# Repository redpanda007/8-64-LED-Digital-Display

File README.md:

# 8*64 LED Digital Display

Welcome to the 8*64 LED Digital Display project repository. This project showcases the design of a large-scale LED matrix display, perfect for digital signage, information boards, or creative lighting installations.

## Project Description

This repository contains the design files for an 8*64 LED digital display. The display consists of a matrix of 8 rows and 64 columns of LEDs, providing a versatile canvas for displaying text, graphics, and animations.

## Design Files

### Schematic Diagram
View the electrical schematic for the LED matrix:
[Schematic Diagram](https://a360.co/3yEBdw0)

### PCB Design
Explore the 2D PCB layout:
[2D PCB Design](https://a360.co/3Mn7vhW)

### 3D PCB Model
Visualize the PCB in 3D:
[3D PCB Design](https://a360.co/4cF3tME)

## Features

- 8*64 LED matrix configuration
- Custom PCB design optimized for LED arrangement
- Scalable design for various display sizes

## Applications

- Public information displays
- Advertising billboards
- Event information boards
- Interactive art installations
- Sports scoreboards

## Getting Started

1. Review the schematic diagram to understand the circuit layout.
2. Examine the 2D PCB design for component placement and routing.
3. Use the 3D PCB model to visualize the final product and plan assembly.

## Contributing

We welcome contributions to improve the design or documentation. Please follow these steps:

1. Fork the repository
2. Create a new branch (`git checkout -b feature/AmazingFeature`)
3. Commit your changes (`git commit -m 'Add some AmazingFeature'`)
4. Push to the branch (`git push origin feature/AmazingFeature`)
5. Open a Pull Request

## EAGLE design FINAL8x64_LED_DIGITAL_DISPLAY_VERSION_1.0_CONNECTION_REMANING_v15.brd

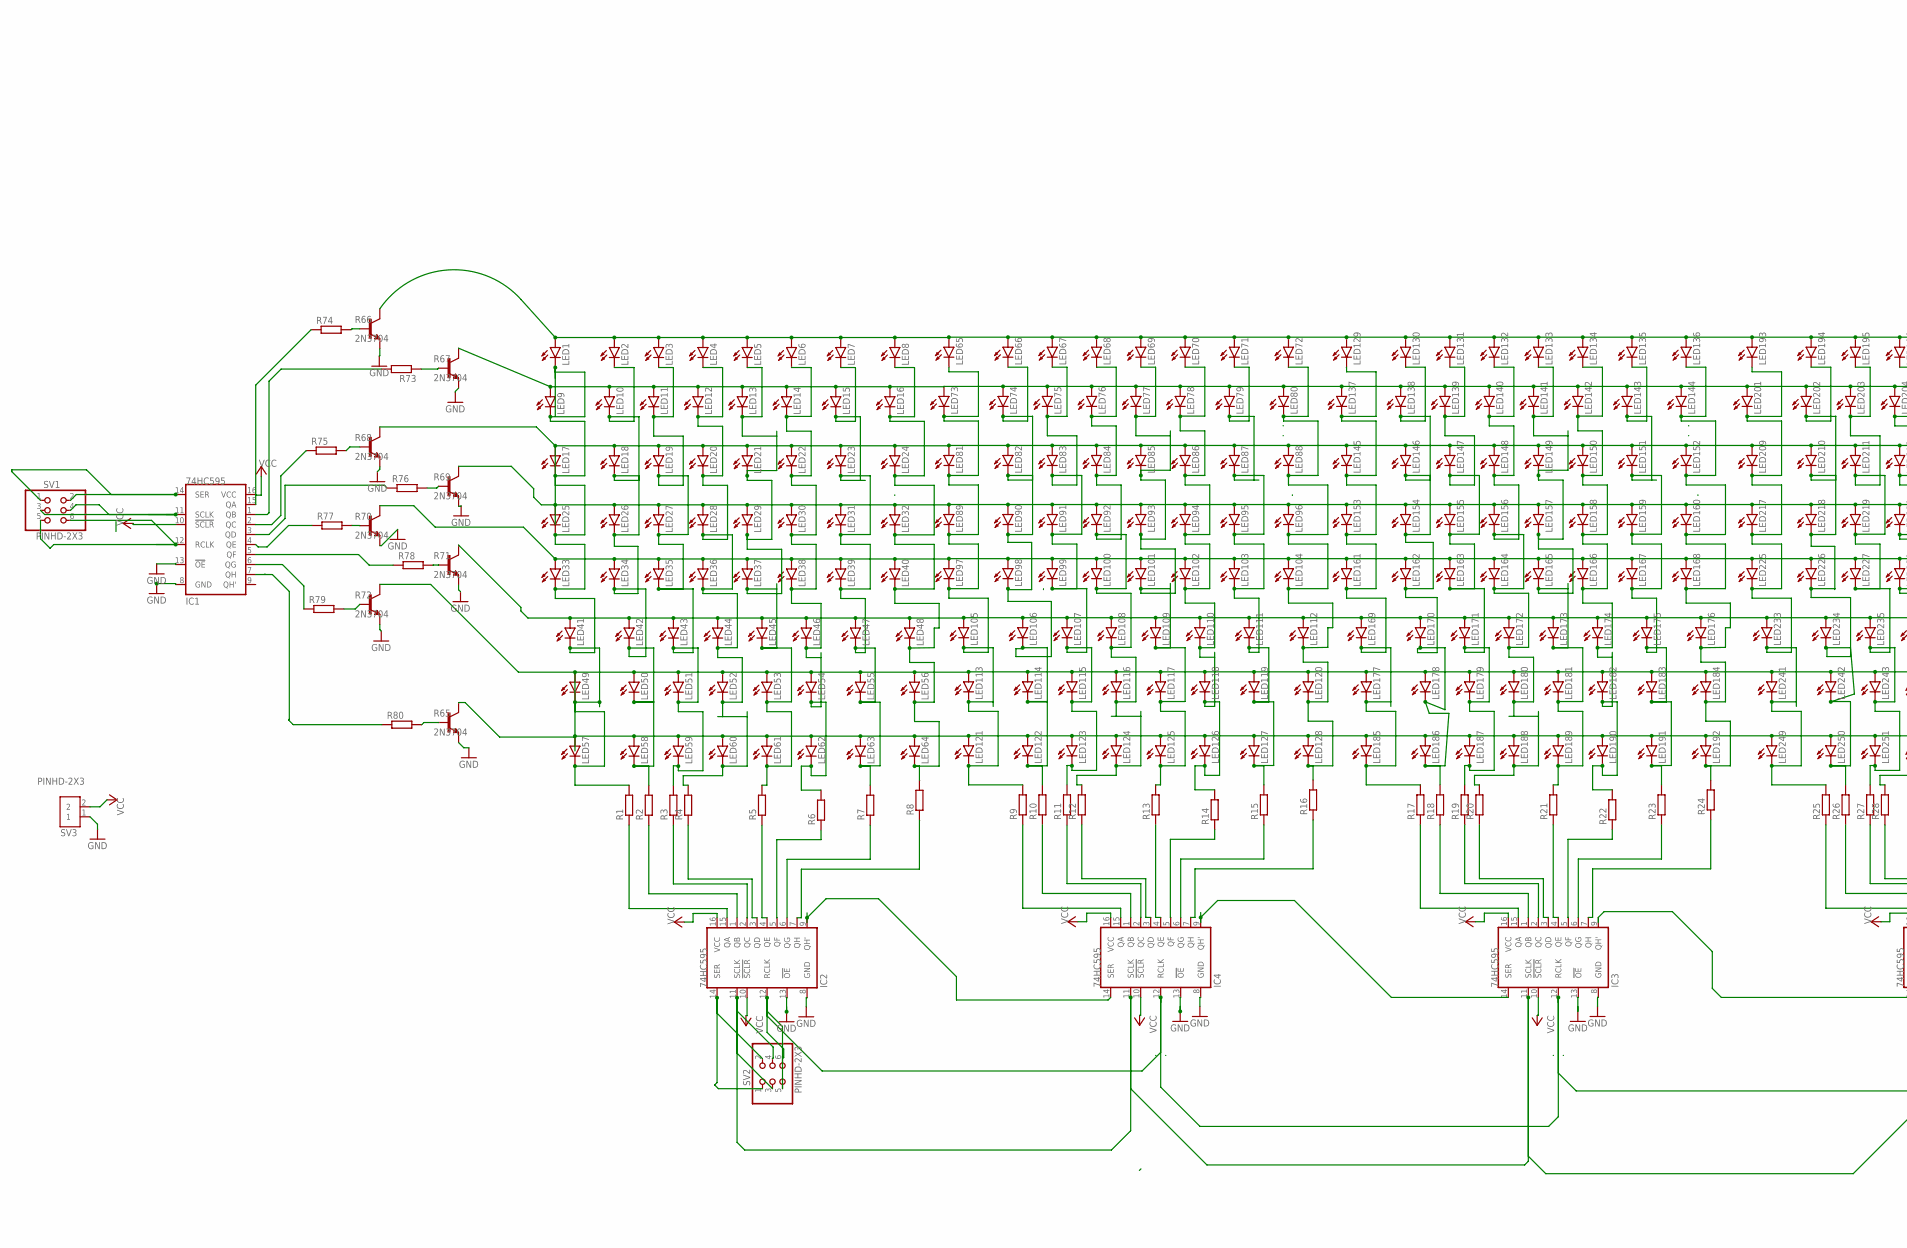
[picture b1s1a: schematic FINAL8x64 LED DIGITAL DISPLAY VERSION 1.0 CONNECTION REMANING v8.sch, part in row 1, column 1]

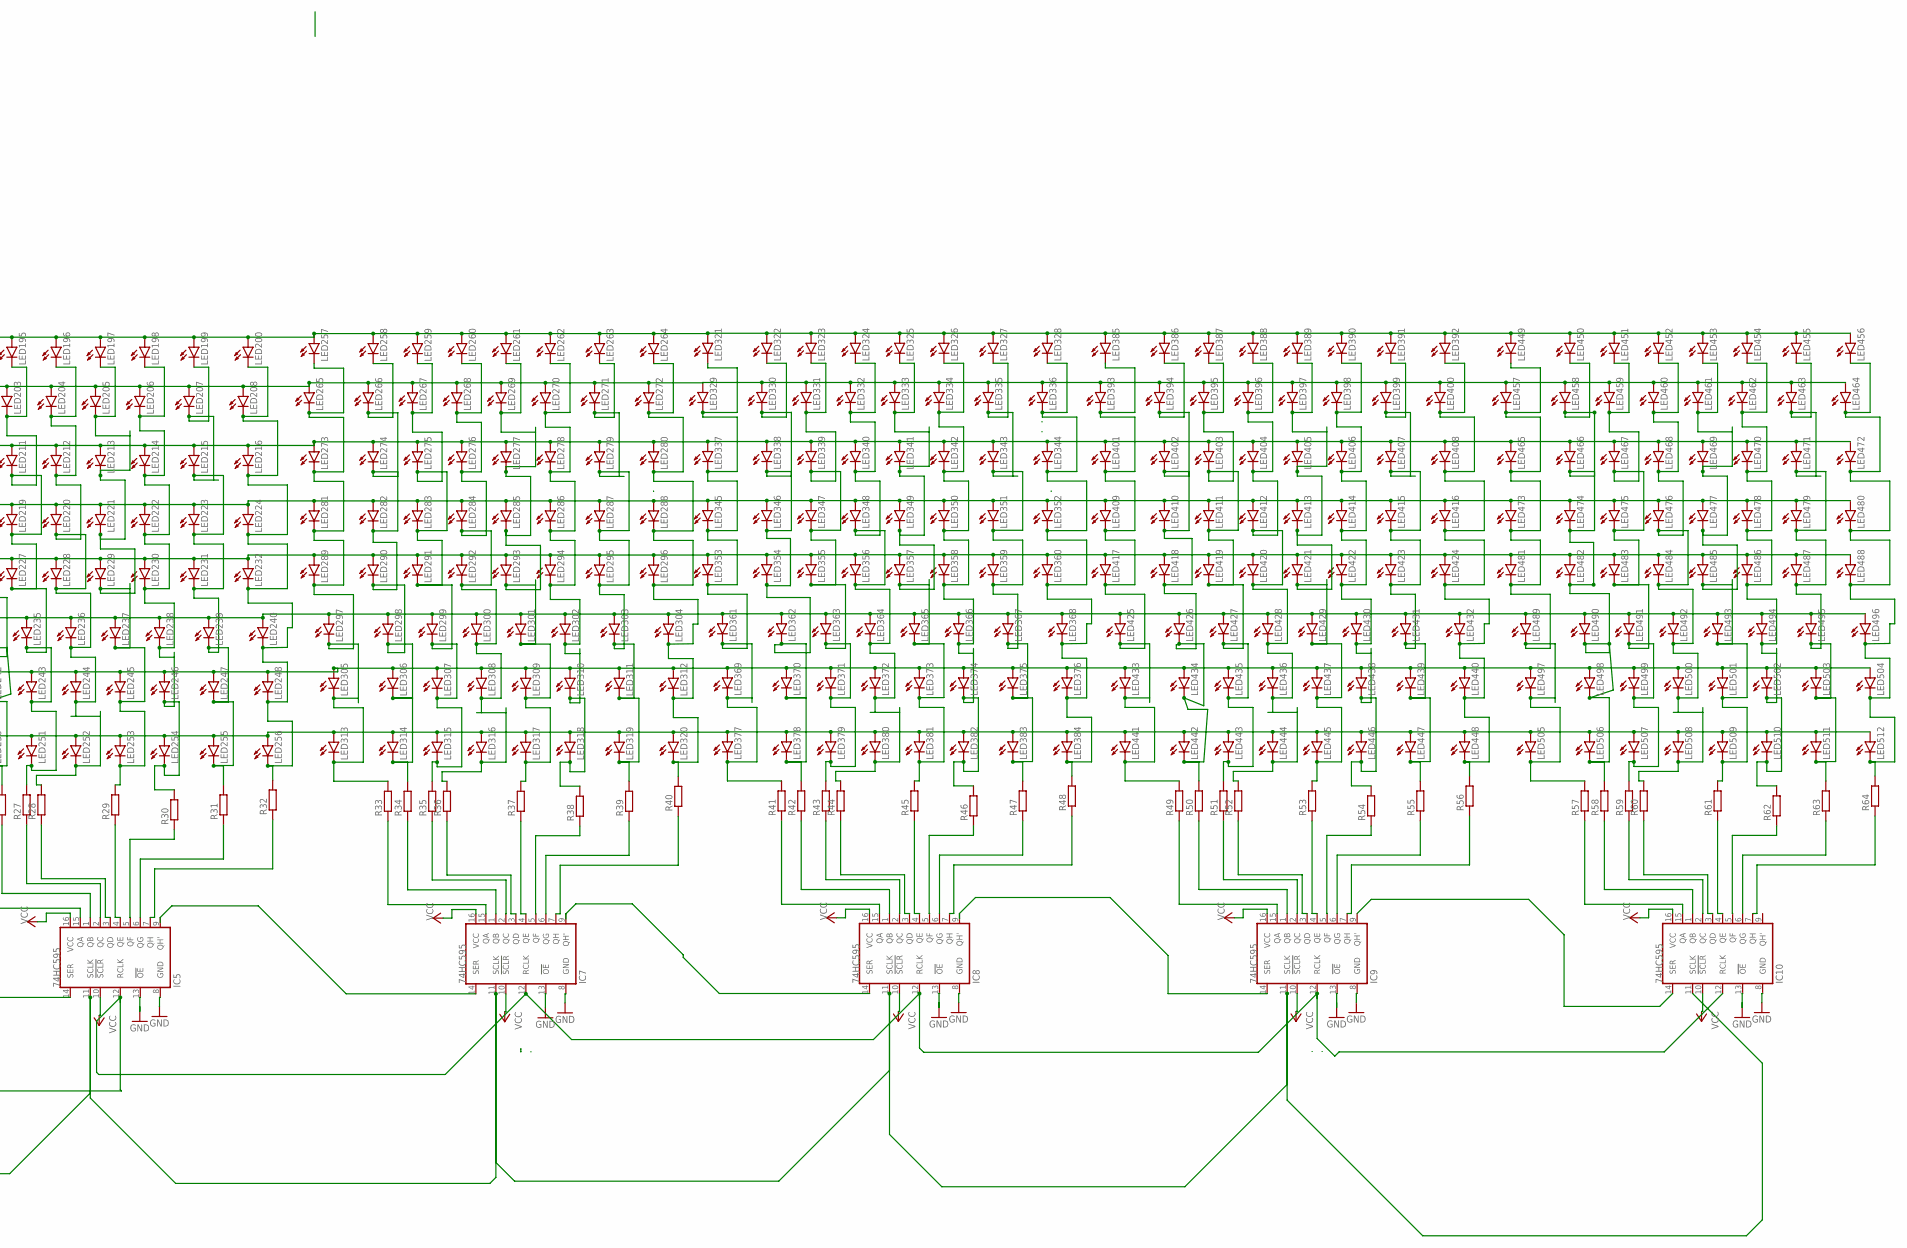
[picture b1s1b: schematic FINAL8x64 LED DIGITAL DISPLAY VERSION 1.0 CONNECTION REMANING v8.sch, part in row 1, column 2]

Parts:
IC1, IC2, IC3, IC4, IC5, IC7, IC8, IC9, IC10: 74HC595; SO16
LED1, LED2, LED3, LED4, LED5, LED6, LED7, LED8, LED9, LED10, LED11, LED12, LED13, LED14, LED15, LED16, LED17, LED18, LED19, LED20, LED21, LED22, LED23, LED24, LED25, LED26, LED27, LED28, LED29, LED30, LED31, LED32, LED33, LED34, LED35, LED36, LED37, LED38, LED39, LED40, LED41, LED42, LED43, LED44, LED45, LED46, LED47, LED48, LED49, LED50, LED51, LED52, LED53, LED54, LED55, LED56, LED57, LED58, LED59, LED60, LED61, LED62, LED63, LED64, LED65, LED66, LED67, LED68, LED69, LED70, LED71, LED72, LED73, LED74, LED75, LED76, LED77, LED78, LED79, LED80, LED81, LED82, LED83, LED84, LED85, LED86, LED87, LED88, LED89, LED90, LED91, LED92, LED93, LED94, LED95, LED96, LED97, LED98, LED99, LED100, LED101, LED102, LED103, LED104, LED105, LED106, LED107, LED108, LED109, LED110, LED111, LED112, LED113, LED114, LED115, LED116, LED117, LED118, LED119, LED120, LED121, LED122, LED123, LED124, LED125, LED126, LED127, LED128, LED129, LED130, LED131, LED132, LED133, LED134, LED135, LED136, LED137, LED138, LED139, LED140, LED141, LED142, LED143, LED144, LED145, LED146, LED147, LED148, LED149, LED150, LED151, LED152, LED153, LED154, LED155, LED156, LED157, LED158, LED159, LED160, LED161, LED162, LED163, LED164, LED165, LED166, LED167, LED168, LED169, LED170, LED171, LED172, LED173, LED174, LED175, LED176, LED177, LED178, LED179, LED180, LED181, LED182, LED183, LED184, LED185, LED186, LED187, LED188, LED189, LED190, LED191, LED192, LED193, LED194, LED195, LED196, LED197, LED198, LED199, LED200, LED201, LED202, LED203, LED204, LED205, LED206, LED207, LED208, LED209, LED210, LED211, LED212, LED213, LED214, LED215, LED216, LED217, LED218, LED219, LED220, LED221, LED222, LED223, LED224, LED225, LED226, LED227, LED228, LED229, LED230, LED231, LED232, LED233, LED234, LED235, LED236, LED237, LED238, LED239, LED240, LED241, LED242, LED243, LED244, LED245, LED246, LED247, LED248, LED249, LED250, LED251, LED252, LED253, LED254, LED255, LED256, LED257, LED258, LED259, LED260, LED261, LED262, LED263, LED264, LED265, LED266, LED267, LED268, LED269, LED270, LED271, LED272, LED273, LED274, LED275, LED276, LED277, LED278, LED279, LED280, LED281, LED282, LED283, LED284, LED285, LED286, LED287, LED288, LED289, LED290, LED291, LED292, LED293, LED294, LED295, LED296, LED297, LED298, LED299, LED300, LED301, LED302, LED303, LED304, LED305, LED306, LED307, LED308, LED309, LED310, LED311, LED312, LED313, LED314, LED315, LED316, LED317, LED318, LED319, LED320, LED321, LED322, LED323, LED324, LED325, LED326, LED327, LED328, LED329, LED330, LED331, LED332, LED333, LED334, LED335, LED336, LED337, LED338, LED339, LED340, LED341, LED342, LED343, LED344, LED345, LED346, LED347, LED348, LED349, LED350, LED351, LED352, LED353, LED354, LED355, LED356, LED357, LED358, LED359, LED360, LED361, LED362, LED363, LED364, LED365, LED366, LED367, LED368, LED369, LED370, LED371, LED372, LED373, LED374, LED375, LED376, LED377, LED378, LED379, LED380, LED381, LED382, LED383, LED384, LED385, LED386, LED387, LED388, LED389, LED390, LED391, LED392, LED393, LED394, LED395, LED396, LED397, LED398, LED399, LED400, LED401, LED402, LED403, LED404, LED405, LED406, LED407, LED408, LED409, LED410, LED411, LED412, LED413, LED414, LED415, LED416, LED417, LED418, LED419, LED420, LED421, LED422, LED423, LED424, LED425, LED426, LED427, LED428, LED429, LED430, LED431, LED432, LED433, LED434, LED435, LED436, LED437, LED438, LED439, LED440, LED441, LED442, LED443, LED444, LED445, LED446, LED447, LED448, LED449, LED450, LED451, LED452, LED453, LED454, LED455, LED456, LED457, LED458, LED459, LED460, LED461, LED462, LED463, LED464, LED465, LED466, LED467, LED468, LED469, LED470, LED471, LED472, LED473, LED474, LED475, LED476, LED477, LED478, LED479, LED480, LED481, LED482, LED483, LED484, LED485, LED486, LED487, LED488, LED489, LED490, LED491, LED492, LED493, LED494, LED495, LED496, LED497, LED498, LED499, LED500, LED501, LED502, LED503, LED504, LED505, LED506, LED507, LED508, LED509, LED510, LED511, LED512: LED5MM
R1, R2, R3, R4, R5, R6, R7, R8, R9, R10, R11, R12, R13, R14, R15, R16, R17, R18, R19, R20, R21, R22, R23, R24, R25, R26, R27, R28, R29, R30, R31, R32, R33, R34, R35, R36, R37, R38, R39, R40, R41, R42, R43, R44, R45, R46, R47, R48, R49, R50, R51, R52, R53, R54, R55, R56, R57, R58, R59, R60, R61, R62, R63, R64, R73, R74, R75, R76, R77, R78, R79, R80: R-EU_0204/7; 0204/7
R65, R66, R67, R68, R69, R70, R71, R72: 2N3704; TO92
SV1, SV2: PINHD-2X3; 2X03
SV3: PINHD-2X3; TERMBLK_508-2N

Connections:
GND: IC1.8 (GND), IC1.13 (!OE), IC2.8 (GND), IC2.13 (!OE), IC3.8 (GND), IC3.13 (!OE), IC4.8 (GND), IC4.13 (!OE), IC5.8 (GND), IC5.13 (!OE), IC7.8 (GND), IC7.13 (!OE), IC8.8 (GND), IC8.13 (!OE), IC9.8 (GND), IC9.13 (!OE), IC10.8 (GND), IC10.13 (!OE), R65.3 (E), R66.3 (E), R67.3 (E), R68.3 (E), R69.3 (E), R70.3 (E), R71.3 (E), R72.3 (E), SV3.1
unnamed: R68.1 (B), R75.2
unnamed: LED9.A, LED10.A, LED11.A, LED12.A, LED13.A, LED14.A, LED15.A, LED16.A, LED73.A, LED74.A, LED75.A, LED76.A, LED77.A, LED78.A, LED79.A, LED80.A, LED137.A, LED138.A, LED139.A, LED140.A, LED141.A, LED142.A, LED143.A, LED144.A, LED201.A, LED202.A, LED203.A, LED204.A, LED205.A, LED206.A, LED207.A, LED208.A, LED265.A, LED266.A, LED267.A, LED268.A, LED269.A, LED270.A, LED271.A, LED272.A, LED329.A, LED330.A, LED331.A, LED332.A, LED333.A, LED334.A, LED335.A, LED336.A, LED393.A, LED394.A, LED395.A, LED396.A, LED397.A, LED398.A, LED399.A, LED400.A, LED457.A, LED458.A, LED459.A, LED460.A, LED461.A, LED462.A, LED463.A, LED464.A, R67.2 (C)
unnamed: IC2.9 (QH'), IC4.14 (SER)
unnamed: LED17.A, LED18.A, LED19.A, LED20.A, LED21.A, LED22.A, LED23.A, LED24.A, LED25.A, LED26.A, LED27.A, LED28.A, LED29.A, LED30.A, LED31.A, LED32.A, LED81.A, LED82.A, LED83.A, LED84.A, LED85.A, LED86.A, LED87.A, LED88.A, LED89.A, LED90.A, LED91.A, LED92.A, LED93.A, LED94.A, LED95.A, LED96.A, LED145.A, LED146.A, LED147.A, LED148.A, LED149.A, LED150.A, LED151.A, LED152.A, LED153.A, LED154.A, LED155.A, LED156.A, LED157.A, LED158.A, LED159.A, LED160.A, LED209.A, LED210.A, LED211.A, LED212.A, LED213.A, LED214.A, LED215.A, LED216.A, LED217.A, LED218.A, LED219.A, LED220.A, LED221.A, LED222.A, LED223.A, LED224.A, LED273.A, LED274.A, LED275.A, LED276.A, LED277.A, LED278.A, LED279.A, LED280.A, LED281.A, LED282.A, LED283.A, LED284.A, LED285.A, LED286.A, LED287.A, LED288.A, LED337.A, LED338.A, LED339.A, LED340.A, LED341.A, LED342.A, LED343.A, LED344.A, LED345.A, LED346.A, LED347.A, LED348.A, LED349.A, LED350.A, LED351.A, LED352.A, LED401.A, LED402.A, LED403.A, LED404.A, LED405.A, LED406.A, LED407.A, LED408.A, LED409.A, LED410.A, LED411.A, LED412.A, LED413.A, LED414.A, LED415.A, LED416.A, LED465.A, LED466.A, LED467.A, LED468.A, LED469.A, LED470.A, LED471.A, LED472.A, LED473.A, LED474.A, LED475.A, LED476.A, LED477.A, LED478.A, LED479.A, LED480.A, R68.2 (C), R69.2 (C)
unnamed: LED33.A, LED34.A, LED35.A, LED36.A, LED37.A, LED38.A, LED39.A, LED40.A, LED97.A, LED98.A, LED99.A, LED100.A, LED101.A, LED102.A, LED103.A, LED104.A, LED161.A, LED162.A, LED163.A, LED164.A, LED165.A, LED166.A, LED167.A, LED168.A, LED225.A, LED226.A, LED227.A, LED228.A, LED229.A, LED230.A, LED231.A, LED232.A, LED289.A, LED290.A, LED291.A, LED292.A, LED293.A, LED294.A, LED295.A, LED296.A, LED353.A, LED354.A, LED355.A, LED356.A, LED357.A, LED358.A, LED359.A, LED360.A, LED417.A, LED418.A, LED419.A, LED420.A, LED421.A, LED422.A, LED423.A, LED424.A, LED481.A, LED482.A, LED483.A, LED484.A, LED485.A, LED486.A, LED487.A, LED488.A, R70.2 (C)
unnamed: IC1.15 (QA), R74.1
unnamed: IC3.9 (QH'), IC5.14 (SER)
unnamed: IC1.1 (QB), R73.2
unnamed: LED1.A, LED2.A, LED3.A, LED4.A, LED5.A, LED6.A, LED7.A, LED8.A, LED65.A, LED66.A, LED67.A, LED68.A, LED69.A, LED70.A, LED71.A, LED72.A, LED129.A, LED130.A, LED131.A, LED132.A, LED133.A, LED134.A, LED135.A, LED136.A, LED193.A, LED194.A, LED195.A, LED196.A, LED197.A, LED198.A, LED199.A, LED200.A, LED257.A, LED258.A, LED259.A, LED260.A, LED261.A, LED262.A, LED263.A, LED264.A, LED321.A, LED322.A, LED323.A, LED324.A, LED325.A, LED326.A, LED327.A, LED328.A, LED385.A, LED386.A, LED387.A, LED388.A, LED389.A, LED390.A, LED391.A, LED392.A, LED449.A, LED450.A, LED451.A, LED452.A, LED453.A, LED454.A, LED455.A, LED456.A, R66.2 (C)
unnamed: LED3.K (C), LED11.K (C), LED19.K (C), LED27.K (C), LED35.K (C), LED43.K (C), LED51.K (C), LED59.K (C), R3.2
unnamed: LED4.K (C), LED12.K (C), LED20.K (C), LED28.K (C), LED36.K (C), LED44.K (C), LED52.K (C), LED60.K (C), R4.2
unnamed: LED2.K (C), LED10.K (C), LED18.K (C), LED26.K (C), LED34.K (C), LED42.K (C), LED50.K (C), LED58.K (C), R2.2
unnamed: LED5.K (C), LED13.K (C), LED21.K (C), LED29.K (C), LED37.K (C), LED45.K (C), LED53.K (C), LED61.K (C), R5.2
unnamed: LED6.K (C), LED14.K (C), LED22.K (C), LED30.K (C), LED38.K (C), LED46.K (C), LED54.K (C), LED62.K (C), R6.2
unnamed: LED7.K (C), LED15.K (C), LED23.K (C), LED31.K (C), LED39.K (C), LED47.K (C), LED55.K (C), LED63.K (C), R7.2
unnamed: LED8.K (C), LED16.K (C), LED24.K (C), LED32.K (C), LED40.K (C), LED48.K (C), LED56.K (C), LED64.K (C), R8.2
unnamed: IC2.15 (QA), R1.1
unnamed: IC2.1 (QB), R2.1
unnamed: IC2.2 (QC), R3.1
unnamed: IC2.3 (QD), R4.1
unnamed: IC2.4 (QE), R5.1
unnamed: IC2.5 (QF), R6.1
unnamed: IC2.6 (QG), R7.1
unnamed: IC2.7 (QH), R8.1
unnamed: IC2.14 (SER), SV2.1, SV2.2
unnamed: IC2.11 (SCLK), IC3.11 (SCLK), IC4.11 (SCLK), IC5.11 (SCLK), IC7.11 (SCLK), IC8.11 (SCLK), IC9.11 (SCLK), IC10.11 (SCLK), SV2.3
unnamed: IC5.9 (QH'), IC7.14 (SER)
unnamed: IC1.11 (SCLK), SV1.3, SV1.4
unnamed: LED1.K (C), LED9.K (C), LED17.K (C), LED25.K (C), LED33.K (C), LED41.K (C), LED49.K (C), LED57.K (C), R1.2
unnamed: IC1.12 (RCLK), SV1.5, SV1.6
unnamed: IC2.12 (RCLK), IC3.12 (RCLK), IC4.12 (RCLK), IC5.12 (RCLK), IC7.12 (RCLK), IC8.12 (RCLK), IC9.12 (RCLK), IC10.12 (RCLK), SV2.5, SV2.6
unnamed: IC1.3 (QD), R76.1
unnamed: R66.1 (B), R74.2
unnamed: R71.1 (B), R78.2
unnamed: LED41.A, LED42.A, LED43.A, LED44.A, LED45.A, LED46.A, LED47.A, LED48.A, LED105.A, LED106.A, LED107.A, LED108.A, LED109.A, LED110.A, LED111.A, LED112.A, LED169.A, LED170.A, LED171.A, LED172.A, LED173.A, LED174.A, LED175.A, LED176.A, LED233.A, LED234.A, LED235.A, LED236.A, LED237.A, LED238.A, LED239.A, LED240.A, LED297.A, LED298.A, LED299.A, LED300.A, LED301.A, LED302.A, LED303.A, LED304.A, LED361.A, LED362.A, LED363.A, LED364.A, LED365.A, LED366.A, LED367.A, LED368.A, LED425.A, LED426.A, LED427.A, LED428.A, LED429.A, LED430.A, LED431.A, LED432.A, LED489.A, LED490.A, LED491.A, LED492.A, LED493.A, LED494.A, LED495.A, LED496.A, R71.2 (C)
unnamed: LED49.A, LED50.A, LED51.A, LED52.A, LED53.A, LED54.A, LED55.A, LED56.A, LED57.A, LED58.A, LED59.A, LED60.A, LED61.A, LED62.A, LED63.A, LED64.A, LED113.A, LED114.A, LED115.A, LED116.A, LED117.A, LED118.A, LED119.A, LED120.A, LED121.A, LED122.A, LED123.A, LED124.A, LED125.A, LED126.A, LED127.A, LED128.A, LED177.A, LED178.A, LED179.A, LED180.A, LED181.A, LED182.A, LED183.A, LED184.A, LED185.A, LED186.A, LED187.A, LED188.A, LED189.A, LED190.A, LED191.A, LED192.A, LED241.A, LED242.A, LED243.A, LED244.A, LED245.A, LED246.A, LED247.A, LED248.A, LED249.A, LED250.A, LED251.A, LED252.A, LED253.A, LED254.A, LED255.A, LED256.A, LED305.A, LED306.A, LED307.A, LED308.A, LED309.A, LED310.A, LED311.A, LED312.A, LED313.A, LED314.A, LED315.A, LED316.A, LED317.A, LED318.A, LED319.A, LED320.A, LED369.A, LED370.A, LED371.A, LED372.A, LED373.A, LED374.A, LED375.A, LED376.A, LED377.A, LED378.A, LED379.A, LED380.A, LED381.A, LED382.A, LED383.A, LED384.A, LED433.A, LED434.A, LED435.A, LED436.A, LED437.A, LED438.A, LED439.A, LED440.A, LED441.A, LED442.A, LED443.A, LED444.A, LED445.A, LED446.A, LED447.A, LED448.A, LED497.A, LED498.A, LED499.A, LED500.A, LED501.A, LED502.A, LED503.A, LED504.A, LED505.A, LED506.A, LED507.A, LED508.A, LED509.A, LED510.A, LED511.A, LED512.A, R65.2 (C), R72.2 (C)
unnamed: LED257.K (C), LED265.K (C), LED273.K (C), LED281.K (C), LED289.K (C), LED297.K (C), LED305.K (C), LED313.K (C), R33.2
unnamed: LED65.K (C), LED73.K (C), LED81.K (C), LED89.K (C), LED97.K (C), LED105.K (C), LED113.K (C), LED121.K (C), R9.2
unnamed: LED194.K (C), LED202.K (C), LED210.K (C), LED218.K (C), LED226.K (C), LED234.K (C), LED242.K (C), LED250.K (C), R26.2
unnamed: LED67.K (C), LED75.K (C), LED83.K (C), LED91.K (C), LED99.K (C), LED107.K (C), LED115.K (C), LED123.K (C), R11.2
unnamed: LED68.K (C), LED76.K (C), LED84.K (C), LED92.K (C), LED100.K (C), LED108.K (C), LED116.K (C), LED124.K (C), R12.2
unnamed: LED69.K (C), LED77.K (C), LED85.K (C), LED93.K (C), LED101.K (C), LED109.K (C), LED117.K (C), LED125.K (C), R13.2
unnamed: LED70.K (C), LED78.K (C), LED86.K (C), LED94.K (C), LED102.K (C), LED110.K (C), LED118.K (C), LED126.K (C), R14.2
unnamed: LED71.K (C), LED79.K (C), LED87.K (C), LED95.K (C), LED103.K (C), LED111.K (C), LED119.K (C), LED127.K (C), R15.2
unnamed: LED72.K (C), LED80.K (C), LED88.K (C), LED96.K (C), LED104.K (C), LED112.K (C), LED120.K (C), LED128.K (C), R16.2
unnamed: IC4.15 (QA), R9.1
unnamed: IC4.1 (QB), R10.1
unnamed: IC4.2 (QC), R11.1
unnamed: IC4.3 (QD), R12.1
unnamed: IC4.4 (QE), R13.1
unnamed: IC4.5 (QF), R14.1
unnamed: IC4.6 (QG), R15.1
unnamed: IC4.7 (QH), R16.1
unnamed: IC7.9 (QH'), IC8.14 (SER)
unnamed: IC1.2 (QC), R75.1
unnamed: LED258.K (C), LED266.K (C), LED274.K (C), LED282.K (C), LED290.K (C), LED298.K (C), LED306.K (C), LED314.K (C), R34.2
unnamed: IC3.14 (SER), IC4.9 (QH')
unnamed: LED66.K (C), LED74.K (C), LED82.K (C), LED90.K (C), LED98.K (C), LED106.K (C), LED114.K (C), LED122.K (C), R10.2
unnamed: LED259.K (C), LED267.K (C), LED275.K (C), LED283.K (C), LED291.K (C), LED299.K (C), LED307.K (C), LED315.K (C), R35.2
unnamed: LED260.K (C), LED268.K (C), LED276.K (C), LED284.K (C), LED292.K (C), LED300.K (C), LED308.K (C), LED316.K (C), R36.2
unnamed: LED261.K (C), LED269.K (C), LED277.K (C), LED285.K (C), LED293.K (C), LED301.K (C), LED309.K (C), LED317.K (C), R37.2
unnamed: LED262.K (C), LED270.K (C), LED278.K (C), LED286.K (C), LED294.K (C), LED302.K (C), LED310.K (C), LED318.K (C), R38.2
unnamed: LED263.K (C), LED271.K (C), LED279.K (C), LED287.K (C), LED295.K (C), LED303.K (C), LED311.K (C), LED319.K (C), R39.2
unnamed: LED129.K (C), LED137.K (C), LED145.K (C), LED153.K (C), LED161.K (C), LED169.K (C), LED177.K (C), LED185.K (C), R17.2
unnamed: LED130.K (C), LED138.K (C), LED146.K (C), LED154.K (C), LED162.K (C), LED170.K (C), LED178.K (C), LED186.K (C), R18.2
unnamed: LED131.K (C), LED139.K (C), LED147.K (C), LED155.K (C), LED163.K (C), LED171.K (C), LED179.K (C), LED187.K (C), R19.2
unnamed: LED132.K (C), LED140.K (C), LED148.K (C), LED156.K (C), LED164.K (C), LED172.K (C), LED180.K (C), LED188.K (C), R20.2
unnamed: LED133.K (C), LED141.K (C), LED149.K (C), LED157.K (C), LED165.K (C), LED173.K (C), LED181.K (C), LED189.K (C), R21.2
unnamed: LED134.K (C), LED142.K (C), LED150.K (C), LED158.K (C), LED166.K (C), LED174.K (C), LED182.K (C), LED190.K (C), R22.2
unnamed: LED135.K (C), LED143.K (C), LED151.K (C), LED159.K (C), LED167.K (C), LED175.K (C), LED183.K (C), LED191.K (C), R23.2
unnamed: LED136.K (C), LED144.K (C), LED152.K (C), LED160.K (C), LED168.K (C), LED176.K (C), LED184.K (C), LED192.K (C), R24.2
unnamed: IC3.15 (QA), R17.1
unnamed: IC3.1 (QB), R18.1
unnamed: IC3.2 (QC), R19.1
unnamed: IC3.3 (QD), R20.1
unnamed: IC3.4 (QE), R21.1
unnamed: IC3.5 (QF), R22.1
unnamed: IC3.6 (QG), R23.1
unnamed: IC3.7 (QH), R24.1
unnamed: IC8.9 (QH'), IC9.14 (SER)
unnamed: IC1.14 (SER), SV1.1, SV1.2
unnamed: IC9.9 (QH'), IC10.14 (SER)
unnamed: LED193.K (C), LED201.K (C), LED209.K (C), LED217.K (C), LED225.K (C), LED233.K (C), LED241.K (C), LED249.K (C), R25.2
unnamed: LED264.K (C), LED272.K (C), LED280.K (C), LED288.K (C), LED296.K (C), LED304.K (C), LED312.K (C), LED320.K (C), R40.2
unnamed: LED195.K (C), LED203.K (C), LED211.K (C), LED219.K (C), LED227.K (C), LED235.K (C), LED243.K (C), LED251.K (C), R27.2
unnamed: LED196.K (C), LED204.K (C), LED212.K (C), LED220.K (C), LED228.K (C), LED236.K (C), LED244.K (C), LED252.K (C), R28.2
unnamed: LED197.K (C), LED205.K (C), LED213.K (C), LED221.K (C), LED229.K (C), LED237.K (C), LED245.K (C), LED253.K (C), R29.2
unnamed: LED198.K (C), LED206.K (C), LED214.K (C), LED222.K (C), LED230.K (C), LED238.K (C), LED246.K (C), LED254.K (C), R30.2
unnamed: LED199.K (C), LED207.K (C), LED215.K (C), LED223.K (C), LED231.K (C), LED239.K (C), LED247.K (C), LED255.K (C), R31.2
unnamed: LED200.K (C), LED208.K (C), LED216.K (C), LED224.K (C), LED232.K (C), LED240.K (C), LED248.K (C), LED256.K (C), R32.2
unnamed: IC5.15 (QA), R25.1
unnamed: IC5.1 (QB), R26.1
unnamed: IC5.2 (QC), R27.1
unnamed: IC5.3 (QD), R28.1
unnamed: IC5.4 (QE), R29.1
unnamed: IC5.5 (QF), R30.1
unnamed: IC5.6 (QG), R31.1
unnamed: IC5.7 (QH), R32.1
unnamed: IC7.15 (QA), R33.1
unnamed: IC7.1 (QB), R34.1
unnamed: IC7.2 (QC), R35.1
unnamed: IC7.3 (QD), R36.1
unnamed: IC7.4 (QE), R37.1
unnamed: IC7.5 (QF), R38.1
unnamed: IC7.6 (QG), R39.1
unnamed: IC7.7 (QH), R40.1
unnamed: R67.1 (B), R73.1
unnamed: R69.1 (B), R76.2
unnamed: R70.1 (B), R77.2
unnamed: IC1.4 (QE), R77.1
unnamed: IC1.5 (QF), R78.1
unnamed: LED321.K (C), LED329.K (C), LED337.K (C), LED345.K (C), LED353.K (C), LED361.K (C), LED369.K (C), LED377.K (C), R41.2
unnamed: LED323.K (C), LED331.K (C), LED339.K (C), LED347.K (C), LED355.K (C), LED363.K (C), LED371.K (C), LED379.K (C), R43.2
unnamed: LED324.K (C), LED332.K (C), LED340.K (C), LED348.K (C), LED356.K (C), LED364.K (C), LED372.K (C), LED380.K (C), R44.2
unnamed: LED325.K (C), LED333.K (C), LED341.K (C), LED349.K (C), LED357.K (C), LED365.K (C), LED373.K (C), LED381.K (C), R45.2
unnamed: LED326.K (C), LED334.K (C), LED342.K (C), LED350.K (C), LED358.K (C), LED366.K (C), LED374.K (C), LED382.K (C), R46.2
unnamed: LED327.K (C), LED335.K (C), LED343.K (C), LED351.K (C), LED359.K (C), LED367.K (C), LED375.K (C), LED383.K (C), R47.2
unnamed: LED328.K (C), LED336.K (C), LED344.K (C), LED352.K (C), LED360.K (C), LED368.K (C), LED376.K (C), LED384.K (C), R48.2
unnamed: IC8.15 (QA), R41.1
unnamed: IC8.1 (QB), R42.1
unnamed: IC8.2 (QC), R43.1
unnamed: IC8.3 (QD), R44.1
unnamed: IC8.4 (QE), R45.1
unnamed: IC8.5 (QF), R46.1
unnamed: IC8.6 (QG), R47.1
unnamed: IC8.7 (QH), R48.1
unnamed: IC1.6 (QG), R79.1
unnamed: LED385.K (C), LED393.K (C), LED401.K (C), LED409.K (C), LED417.K (C), LED425.K (C), LED433.K (C), LED441.K (C), R49.2
unnamed: LED386.K (C), LED394.K (C), LED402.K (C), LED410.K (C), LED418.K (C), LED426.K (C), LED434.K (C), LED442.K (C), R50.2
unnamed: LED387.K (C), LED395.K (C), LED403.K (C), LED411.K (C), LED419.K (C), LED427.K (C), LED435.K (C), LED443.K (C), R51.2
unnamed: LED388.K (C), LED396.K (C), LED404.K (C), LED412.K (C), LED420.K (C), LED428.K (C), LED436.K (C), LED444.K (C), R52.2
unnamed: LED389.K (C), LED397.K (C), LED405.K (C), LED413.K (C), LED421.K (C), LED429.K (C), LED437.K (C), LED445.K (C), R53.2
unnamed: LED390.K (C), LED398.K (C), LED406.K (C), LED414.K (C), LED422.K (C), LED430.K (C), LED438.K (C), LED446.K (C), R54.2
unnamed: LED391.K (C), LED399.K (C), LED407.K (C), LED415.K (C), LED423.K (C), LED431.K (C), LED439.K (C), LED447.K (C), R55.2
unnamed: LED392.K (C), LED400.K (C), LED408.K (C), LED416.K (C), LED424.K (C), LED432.K (C), LED440.K (C), LED448.K (C), R56.2
unnamed: IC9.15 (QA), R49.1
unnamed: IC9.1 (QB), R50.1
unnamed: IC9.2 (QC), R51.1
unnamed: IC9.3 (QD), R52.1
unnamed: IC9.4 (QE), R53.1
unnamed: IC9.5 (QF), R54.1
unnamed: IC9.6 (QG), R55.1
unnamed: IC9.7 (QH), R56.1
unnamed: R72.1 (B), R79.2
unnamed: LED449.K (C), LED457.K (C), LED465.K (C), LED473.K (C), LED481.K (C), LED489.K (C), LED497.K (C), LED505.K (C), R57.2
unnamed: LED451.K (C), LED459.K (C), LED467.K (C), LED475.K (C), LED483.K (C), LED491.K (C), LED499.K (C), LED507.K (C), R59.2
unnamed: LED452.K (C), LED460.K (C), LED468.K (C), LED476.K (C), LED484.K (C), LED492.K (C), LED500.K (C), LED508.K (C), R60.2
unnamed: LED453.K (C), LED461.K (C), LED469.K (C), LED477.K (C), LED485.K (C), LED493.K (C), LED501.K (C), LED509.K (C), R61.2
unnamed: LED454.K (C), LED462.K (C), LED470.K (C), LED478.K (C), LED486.K (C), LED494.K (C), LED502.K (C), LED510.K (C), R62.2
unnamed: LED455.K (C), LED463.K (C), LED471.K (C), LED479.K (C), LED487.K (C), LED495.K (C), LED503.K (C), LED511.K (C), R63.2
unnamed: LED456.K (C), LED464.K (C), LED472.K (C), LED480.K (C), LED488.K (C), LED496.K (C), LED504.K (C), LED512.K (C), R64.2
unnamed: IC10.15 (QA), R57.1
unnamed: IC10.1 (QB), R58.1
unnamed: IC10.2 (QC), R59.1
unnamed: IC10.3 (QD), R60.1
unnamed: IC10.4 (QE), R61.1
unnamed: IC10.5 (QF), R62.1
unnamed: IC10.6 (QG), R63.1
unnamed: IC10.7 (QH), R64.1
unnamed: LED322.K (C), LED330.K (C), LED338.K (C), LED346.K (C), LED354.K (C), LED362.K (C), LED370.K (C), LED378.K (C), R42.2
unnamed: LED450.K (C), LED458.K (C), LED466.K (C), LED474.K (C), LED482.K (C), LED490.K (C), LED498.K (C), LED506.K (C), R58.2
unnamed: IC1.7 (QH), R80.1
unnamed: R65.1 (B), R80.2
VCC: IC1.10 (!SCLR), IC1.16 (VCC), IC2.10 (!SCLR), IC2.16 (VCC), IC3.10 (!SCLR), IC3.16 (VCC), IC4.10 (!SCLR), IC4.16 (VCC), IC5.10 (!SCLR), IC5.16 (VCC), IC7.10 (!SCLR), IC7.16 (VCC), IC8.10 (!SCLR), IC8.16 (VCC), IC9.10 (!SCLR), IC9.16 (VCC), IC10.10 (!SCLR), IC10.16 (VCC), SV3.2

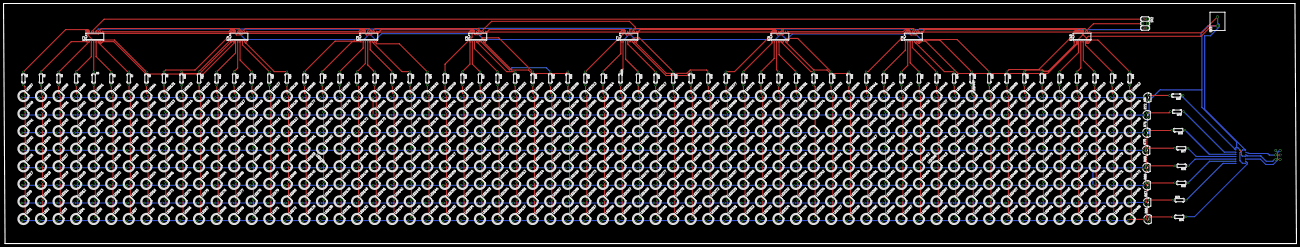
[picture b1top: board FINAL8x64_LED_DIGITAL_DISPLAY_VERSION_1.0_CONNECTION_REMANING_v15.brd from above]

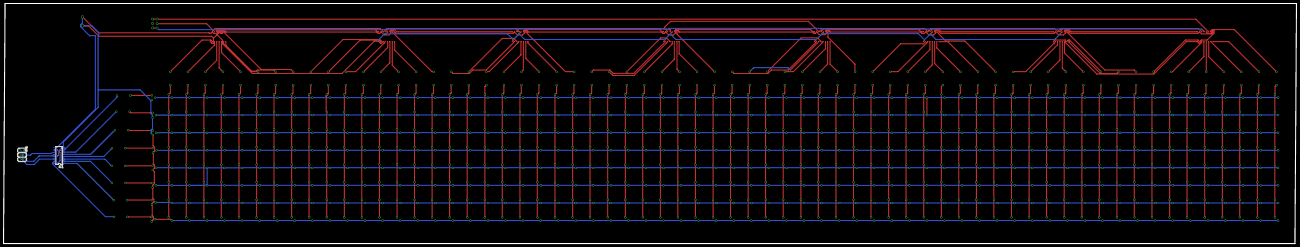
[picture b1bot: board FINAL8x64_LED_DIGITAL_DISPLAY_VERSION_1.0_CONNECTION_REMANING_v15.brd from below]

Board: 2 copper layers, 736.4 x 136.7 mm, 604 parts (2 on the bottom side), 165 nets.
